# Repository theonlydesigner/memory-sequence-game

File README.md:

# Memory Sequence Game

A custom Simon Says-style memory game hardware project featuring an onboard Arduino Nano, multi-colored LED array, tactile pushbuttons and dual haptic/buzzer feedback [because pressing buttons without audio-visual chaos is boring].

## Overview

This project is an all-in-one memory game board built around the Arduino Nano. It combines 4 distinct color LEDs (Red, Green, Blue, Yellow), 4 matching tactile buttons, audio tone generation and vibration feedback into a clean, standalone PCB footprint. Designed for simple assembly, standalone power handling and easy reprogramming.

## Features

* **Dynamic Sequence Generation:** Randomized color patterns generated each level with an integrated countdown timer to force quick decisions.
* **Audio-Haptic Feedback:** Each button press triggers a dedicated pitch note alongside vibration motor/buzzer feedback.
* **Dedicated Power Delivery:** Onboard DC barrel jack and voltage regulator setup to run off external DC power without frying components.
* **Hardware Controls:** Dual slide switches dedicated to master power toggle and volume/feedback control.
* **Repurposable Microcontroller Hub:** Built around female pin headers for the Arduino Nano, allowing the core board to be reused for other dev projects.

## Gallery

### Schematic & Layout

| Schematic Design | PCB 2D Layout Top | PCB 2D Layout Bottom |
| :---: | :---: | :---: |
|  |  |  |

### 3D Model Renders

| Perspective View | Top Isometric |
| :---: | :---: |
|  |  |

| Side Profile | Rear Power & Port Angle |
| :---: | :---: |
|  |  |

## Bill of Materials (BOM)

| Item | Quantity | Description / Package |
| :--- | :---: | :--- |
| **Arduino Nano** | 1 | Microcontroller (with female pin headers) |
| **Colored LEDs** | 4 | 1x Red, 1x Green, 1x Blue, 1x Yellow |
| **Current Limiting Resistors** | 4 | 220Ω through-hole / axial |
| **Tactile Pushbuttons** | 4 | Standard 4-pin momentary switches |
| **Feedback Motor / Buzzer** | 1 | Vibration motor or piezo buzzer |
| **DC Barrel Jack** | 1 | Standard DC power input jack |
| **Slide Switches** | 2 | SPDT switches (Power & Volume controls) |
| **Voltage Regulator** | 1 | Onboard linear voltage regulator |
| **JST Connector** | 1 | Auxiliary power connector |

## How to Assemble

1. **Low-Profile Components:** Solder the 4x 220Ω current-limiting resistors first.
2. **Semiconductors & Switches:** Mount the 4 LEDs (pay attention to anode/cathode orientation), voltage regulator and slide switches.
3. **Interactive Hardware:** Solder the 4 tactile pushbuttons, DC barrel jack, vibration motor/buzzer and JST connector.
4. **Header Sockets:** Solder the female pin headers for the Arduino Nano socket.
5. **Mount & Flash:** Insert the Arduino Nano into the headers, upload the game code via USB-C/Mini-USB and flip the power switch.

## Credits

* **Designer:** Pratham Rupera (`theonlydesigner`)
* **Platform:** Built for Hack Club

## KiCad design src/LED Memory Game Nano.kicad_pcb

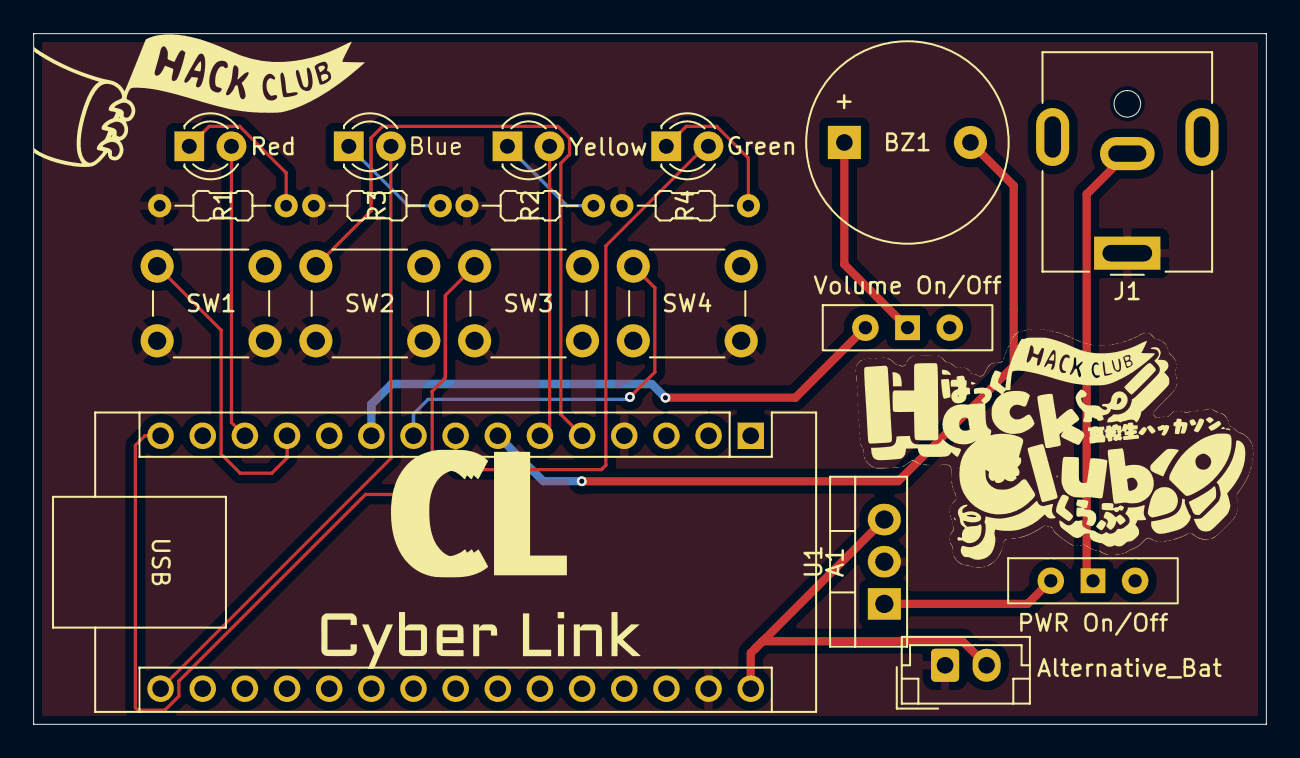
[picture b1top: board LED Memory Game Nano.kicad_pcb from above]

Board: 2 copper layers, 74.3 x 41.6 mm, 19 parts (0 on the bottom side), 19 nets.

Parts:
A1: Arduino_Nano_v3.x; Arduino_Nano
Alternative_Bat: JST_EH_B2B-EH-A_1x02_P2.50mm_Vertical
BZ1: Buzzer; Buzzer_12x9.5RM7.6
D1: Red; LED_D3.0mm
D2: Yellow; LED_D3.0mm
D3: Blue; LED_D3.0mm
D4: Green; LED_D3.0mm
J1: DC Barrel; BarrelJack_CUI_PJ-063AH_Horizontal
PWR On/Off: SW_Wuerth_450301014042; SW_Slide-03_Wuerth-WS-SLTV_10x2.5x6.4_P2.54mm
R1, R2, R3, R4: 220ohm; R_Axial_DIN0204_L3.6mm_D1.6mm_P7.62mm_Horizontal
SW1: R; SW_PUSH_6mm_RW
SW2: G; SW_PUSH_6mm_RW
SW3: B; SW_PUSH_6mm_RW
SW4: Y; SW_PUSH_6mm_RW
U1: LM340AT-5.0; TO-220-3_Vertical
Volume On/Off: SW_Wuerth_450301014042; SW_Slide-03_Wuerth-WS-SLTV_10x2.5x6.4_P2.54mm

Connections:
+5V: A1.27 (+5V), A1.30 (VIN), Alternative_Bat.2, U1.3 (OUT)
B+: A1.10 (D7), Volume On/Off.2 (C)
B-: A1.7 (D4), BZ1.2 (-)
BTN_B: A1.15 (D12), SW3.1 (A), SW3.2 (A)
BTN_G: A1.5 (D2), SW2.1 (A), SW2.2 (A)
BTN_R: A1.12 (D9), SW1.1 (A), SW1.2 (A)
BTN_Y: A1.9 (D6), SW4.1 (A), SW4.2 (A)
DC: PWR On/Off.2 (C), U1.1 (IN)
GND: A1.4 (GND), A1.29 (GND), Alternative_Bat.1, J1.1, R1.2, R2.2, R3.2, R4.2, SW1.3 (B), SW1.4 (B), SW2.3 (B), SW2.4 (B), SW3.3 (B), SW3.4 (B), SW4.3 (B), SW4.4 (B), U1.2
LED_B: A1.16 (D13), D3.2 (A)
LED_G: A1.6 (D3), D2.2 (A)
LED_R: A1.13 (D10), D1.2 (A)
LED_Y: A1.8 (D5), D4.2 (A)
unnamed: BZ1.1 (+), Volume On/Off.1 (B)
unnamed: D1.1 (K), R1.1
unnamed: D2.1 (K), R2.1
unnamed: D3.1 (K), R3.1
unnamed: D4.1 (K), R4.1
unnamed: J1.2, PWR On/Off.1 (B)
